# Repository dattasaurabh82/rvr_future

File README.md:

# rvr_future

#### NOTE: _make sure make sure you have ffmpeg installed on your system (including all necessary encoding libraries like libmp3lame or libx264)_
## This is running on the  server hosting the browserapp. 

## Install required packages:
`sudo npm install --save`

## For secure connection:
### Generate self signed ssl certificates:
```
openssl genrsa -out key.pem
openssl req -new -key key.pem -out csr.pem
openssl x509 -req -days 9999 -in csr.pem -signkey key.pem -out cert.pem
cp key.pem ssl/ && cp csr.pem ssl/ && cp cert.pem ssl/
rm *.pem
```

##### [Notes for installing in ubuntu server]:
`npm install fs-extra --save`
uncomment all the lines that say `..for ubuntu server` and comment `//` out the previous lines. 

##### for mac users, do : `sudo nodemon server.js` . ("Nodemon" is  monitoring tool and you don't have to restart your server everytime). \n
##### for ubuntu users, do: `sudo node server.js`

#### [Notes for harware control setup]
***You need to install the wss server and set up a raspberry pi zero as harware control.
Primarily clone the `/gpio_test/` in Pi and follow the instructions from `camera_img_save_to_server/serial>socket clinet-server/gpio_test/README.md` to seup your pi hardware control server that will talk to ypu web app session.***

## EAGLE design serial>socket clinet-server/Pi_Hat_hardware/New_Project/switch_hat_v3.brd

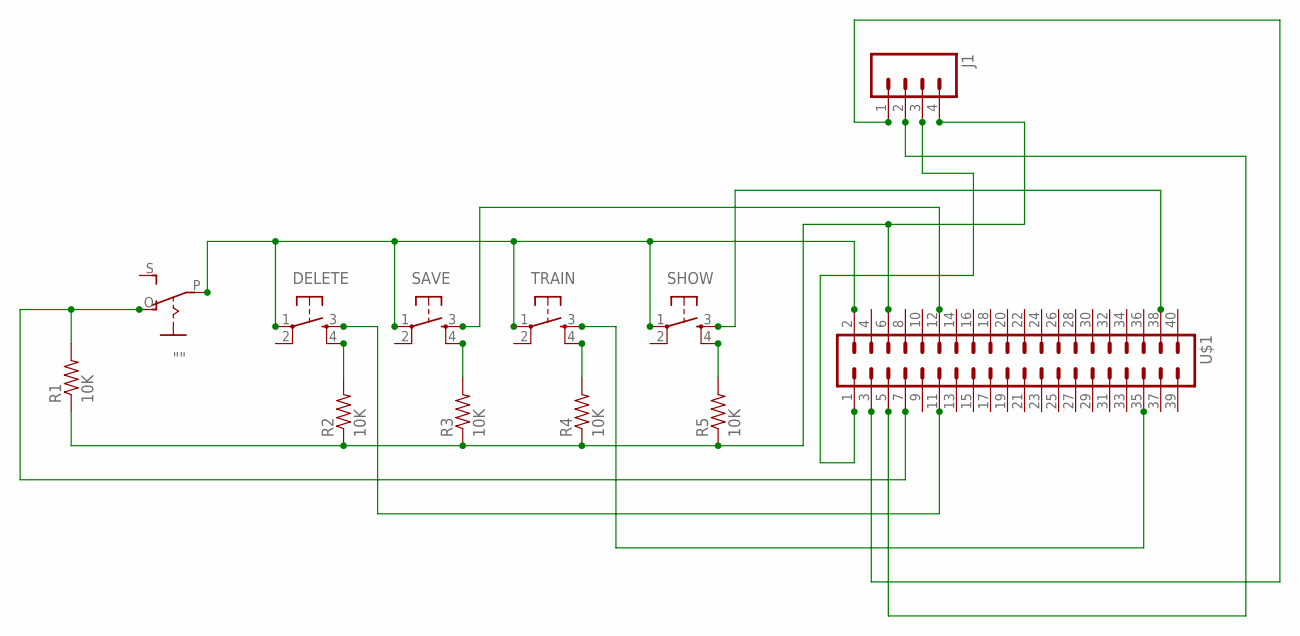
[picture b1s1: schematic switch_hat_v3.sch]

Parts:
"": EG1218S; EG1218
DELETE: TAC_SWITCHPTH; TACTILE-PTH
J1: M04LOCK; 1X04_LOCK
R1, R2, R3, R4, R5: 10K; 0805
SAVE: TAC_SWITCHPTH; TACTILE-PTH
SHOW: TAC_SWITCHPTH; TACTILE-PTH
TRAIN: TAC_SWITCHPTH; TACTILE-PTH
U$1: PIZERO_THROUGH_HOLE; PIZERO_THOUGH_HOLE

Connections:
unnamed: DELETE.4, R2.2
unnamed: R3.2, SAVE.4
unnamed: R4.2, TRAIN.4
unnamed: R5.2, SHOW.4
unnamed: J1.4, R1.1, R2.1, R3.1, R4.1, R5.1, U$1.6
unnamed: DELETE.3, U$1.11
unnamed: SAVE.3, U$1.12
unnamed: J1.2, U$1.5
unnamed: TRAIN.3, U$1.35
unnamed: SHOW.3, U$1.38
unnamed: J1.3, U$1.1
unnamed: "".O, R1.2, U$1.7
unnamed: J1.1, U$1.3
VOLT: "".P, DELETE.1, SAVE.1, SHOW.1, TRAIN.1, U$1.2

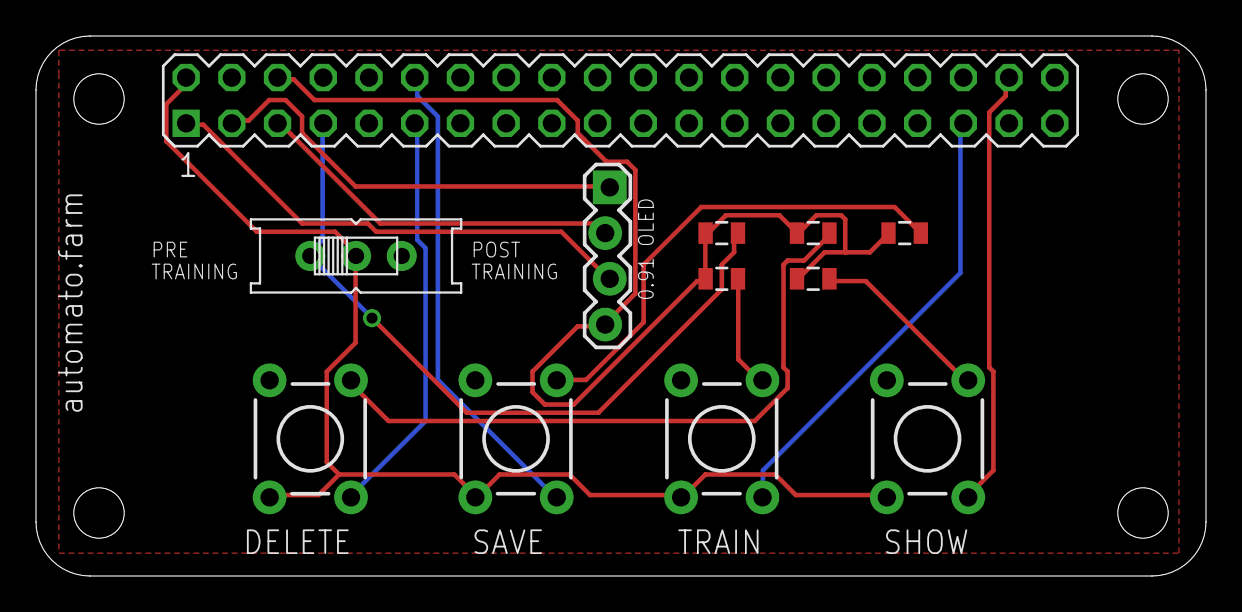
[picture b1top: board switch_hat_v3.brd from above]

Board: 2 copper layers, 65.0 x 30.0 mm, 12 parts (0 on the bottom side), 14 nets.

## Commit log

2017-06-17 updated gitignore
2017-06-17 Updated readme without typo error
2017-06-17 corrected typo
2017-06-17 merging with data folder exclusion
2017-06-17 uploading a picture
2017-06-17 updating with a new picture
2017-06-17 Updated Readme according to new physical interface
2017-06-17 Added hardware design
2017-06-17 Inculded hardware deisgn info in readme
2017-06-17 Added Acreenshot for teh main frontend VR APP . Initial stage
2017-06-17 Updating readme with a preview pic of frontend
2017-06-17 Tint Change

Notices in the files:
parts and their libraries:
SparkFun-Retired: Licensing:Creative Commons ShareAlike 4.0 International - https://creativecommons.org/licenses/by-sa/4.0
